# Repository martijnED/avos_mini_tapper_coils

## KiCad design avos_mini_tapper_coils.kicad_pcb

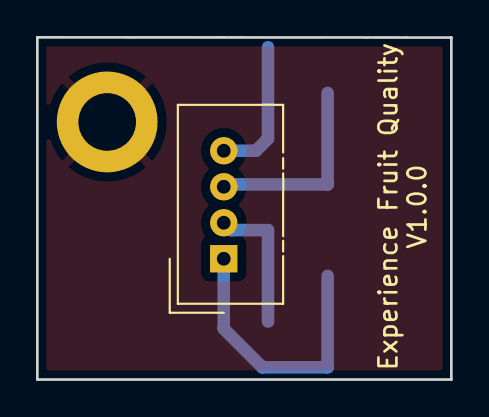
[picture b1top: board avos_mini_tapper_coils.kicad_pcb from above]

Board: 2 copper layers, 23.0 x 19.0 mm, 3 parts (1 on the bottom side), 4 nets.

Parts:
J1: Conn_01x08_Pin; PinHeader_1x08_P2.54mm_Vertical_SMD_Pin1Right
J8: Conn_01x04_Pin; NS-Tech_Grove_1x04_P2mm_Vertical
P8: hole; MountingHole_3.2mm_M3_DIN965_Pad

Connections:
/OUT1: J1.6, J1.8, J8.1
/OUT2: J1.5, J1.7, J8.2
/OUT3: J1.2, J1.4, J8.3
/OUT4: J1.1, J1.3, J8.4

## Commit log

2024-09-02 iAdding first ordered version
